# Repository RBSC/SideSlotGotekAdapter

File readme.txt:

--------------------------------------------
Gotek Adapter Module v1.1
Copyright (c) 2018 RBSC
Portions (c) Talent/Telematica
--------------------------------------------

WARNING! To avoid damage to the adapter and your MSX computer never insert or remove the adapter when a computer is powered on!

IMPORTANT! This adapter is compatible with MSX1, MSX2 and MSX2+ systems. However on MSX1 systems MSX-DOS may not start unless a
memory extension cartridge is inserted into one of the slots. 

IMPORTANT! The Gotek emulator must be secured by at least 2 screws (one from each side) in the adapter's case. Otherwise it will
be detached from the board if pulled by its case.

About
-----

This device is the adapter for the Gotek floppy emulator designed by RBSC based on their own Multicontroller as well as on the
TDC-600 controller that was originally designed by Talent/Telematica. The adapter was specifically made in the form of the side
slot cartidge, that can be used with Yamaha MSX YIS503, CX5M, CX5MII and similar MSX machines. The main idea was to introduce
the possibility to use real floppy disks or their images in the Gotek emulator on these diskless computers.

The adapter can be either used to host the Gotek emulator inside its body or to be used as the controller for the external floppy
disk drives. The Gotek emulator may be also used as the external device.

The adapter may be used with the 50-pin slot on any compatible MSX computer with the special 50-to-60 pin adapter cable or with
the original Yamaha's cartridge-based adapter. Please keep in mind that the Gotek emulator must have the FlashFloppy firmware.
The adapter was tested only with that firmware and the correct functionality is not guaranteed with any other firmware.

Usage with external devices
---------------------------

To be able to use the adapter with external devices, the special cover with holes for the floppy interface connector and for the
power connector must be used. The standard male-to-male 34-pin floppy connector with or without the cable locks should be used to
provide the interface for the external devices. It's recommended to use the connector with the "key" to avoid inserting the
interface cables upside down. As an option, a long floppy cable may be connected directly to the adapter's board (pads marked as
CN2) and stored inside the adapter's case (there's plenty of room there). However it's better to install the through-pin connector
and attach it to the board with wires. Also it may be a good idea to power the floppy drives from external source because certain
MSX computers may not be designed to power floppy drives from their internal power supplies. So if you power older floppy drives
from the adapter's power connector, your MSX's power supply may be loaded beyond its designed capacity. This is a low risk event,
but might still happen.

For the floppy's power connector it's best to use the 4-pin male-to-male audio connector with the lock (those were installed on
the older audio cards to connect them to the audio outputs of the older CD-ROM drives), but other connectors may be used as well.
It's better to use the connectors that can't be connected upside down and, as a result, supply 12v to the 5v circuit - this will
cause severe damage to the Gotek emulator or the floppy drive. This connector must be wired to the PWR pads on the board to provide
both 5v and 12v to the floppy drives. The floppy drives produced in the recent years as well as the Gotek emulator don't need 12v,
but older drives require it.

See the pictures in the PIC subfolder to check the connectors and the wiring of the external devices. Please note that the 720kb
drives must be configured as "A" and the straight floppy cable must be used for them. Those drives must be set as DS0, otherwise
they will not work. For the 1.44mb PC drives with DS1 or DS2 settings a twisted floppy cable must be used. Those PC drives could
be configured as either "A+B" or "B+A". See the "Jumper settings" chapter for more info.

Usage with internal devices
---------------------------

The adapter was originally designed to host the Gotek emulator inside its body. The emulator should be connected to the board
with the 34-pin dual row female connector with long pins. The power could be connected by either using the Molex connector with
its wires soldered to any PWR connector on board or with a single row 4-pin female connector with long pins. It's important to
remember that all internal connectors must have long pins so that they could reach the interface and power connectors of the Gotek
emulator that are located higher than the adapter's board. See the pictures in the PIC subfolder to check the connectors and the
wiring of the inserted Gotek emulator.

Normally the well-soldered power and floppy interface connectors will allow the emulator to be removed from the adapter's case
without too much effort. However inserting the emulator may bend the power connector or get the wrong connection to the floppy
interface pins, so it's highly recommended to open the adapter's case when inserting the emulator to make sure that both power
and interface connectors are properly aligned.

Jumper settings
---------------

The adapter has four 3-pin configuration jumper pins. All 4 of them must have one jumper installed at all times. On the board there
is a CFG table that shows jumper configurations for different drives.

When all 3-pin jumpers are set in the upper position, then a normal 1.44mb PC drive (with default DS1 setting) can be connected to
the board with the standard twisted interface cable. There can be maximum 2 drives connected to the adapter with the same cable. The
drive set as DS1 will be bootable (A:), the drive with DS2 setting will be used as the second drive (B:)

When all 3-pin jumpers are set in the lower position, then a normal 1.44mb PC drive (with default DS1 setting) can be connected to
the board with the standard twisted interface cable. There can be maximum 2 drives connected to the adapter with the same cable. The
drive set as DS2 will be bootable (A:), the drive with DS1 setting will be used as the second drive (B:)

When the 3-pin jumpers are set as shown for the "A" configuration, then a DS/DD 720kb drive set as DS0 or a Gotek emulator set as
DS0 can be connected to the adapter with the straight floppy cable (PC cable with a "twist" won't work). Only one drive may be
connected to the controller in this case. The operating system and certain programs will still allow to use 2 logical drives even if
one drive is connected, but a user will need to change the diskettes or switch the disk images manually when asked.

Selecting BIOS versions
-----------------------

There are 2 versions of disk BIOS available for the adapter - the original one (1.0) and the one translated into English (1.1).
There's a jumper on the board marked as "BIOS VER." that allows to select the desired BIOS version. When the jumper is installed,
the 1.0 version will be used, otherwise the 1.1 version will be used. The version number will be shown when a computer boots into
MSX Basic. Please note that  these BIOSes are capable of working with the 5.25 inch floppy drives, but RBSC was not testing the
adapter with those drives. So if you are using the 5.25 inch drive with the adapter, you are doing this on your own risk.

Notes
-----

The adapter may not load certain games, disk images or boot to certain operating system versions because of the limitations of the
original TDC-600 controller and its firmware. The design of the TDC controller was simplified to have less electronic components,
so its functionality differs from the standard floppy controllers. Certain incompatibility issues will be observed.

The 3D models of the adapter's case, bottom and side cover are provided in the STL format for self-printing. They can be printed on
any 3D printer with PLA or ABS. The recommended settings are 0.2mm layer thickness, supports on, 25% infill, 25% supports, heated
bed and a hood over the printer (to avoid deformations). The case and the bottom cover parts must be printed with their open sides
facing upwards to avoid too many supports and the damage of the screw holders when removing those supports.

The bottom cover should be attached to the body with 3.0mm x 10mm screws with flat heads. It's recommended not to tighten the screws
too much to avoid breaking the threads inside the screw holders. Also keep in mind that the cover is made out of plastic (unlike
the original SFG case's cover), so it needs a bit more gentle handling.

The Gotek emulator needs to be secured inside the adapter's case by two or (better) four 3.0mm x 15mm screws with flat or conical
heads. It's recommended not to tighten the screws too much to avoid breaking the threads inside the Gotek's case.

If you are assembling the adapter with external connectors yourself, please note that it's better to solder the wires between the
board and the connectors. If you use Dupont connectors (like on the images) and jumper pins, you will need to remove the plactic
parts of the pins and cut the 2mm tops of all the pins. Otherwise you won't be able to connect the Dupont connectors to the board. 

IMPORTANT!
----------

The RBSC provides all the files and information for free, without any liability (see the disclaimer.txt file). The provided information,
software or hardware must not be used for commercial purposes unless permitted by the RBSC. Producing a small amount of bare boards for
personal projects and selling the rest of the batch is allowed without the permission of RBSC.

When the sources of the tools are used to create alternative projects, please always mention the original source and the copyright!

Contact information
-------------------

The members of RBSC group Wierzbowsky, Tnt23, Ptero, Pencioner and DJS3000 can be contacted via the MSX.ORG or ZX-PK.RU forums. Just
send a personal message and state your business.

The RBSC repository can be found here:

https://github.com/rbsc

The MSX-related 3D models published by RBSC can be found here:

https://www.thingiverse.com/groups/rbsc/things

-= ! MSX FOREVER ! =-

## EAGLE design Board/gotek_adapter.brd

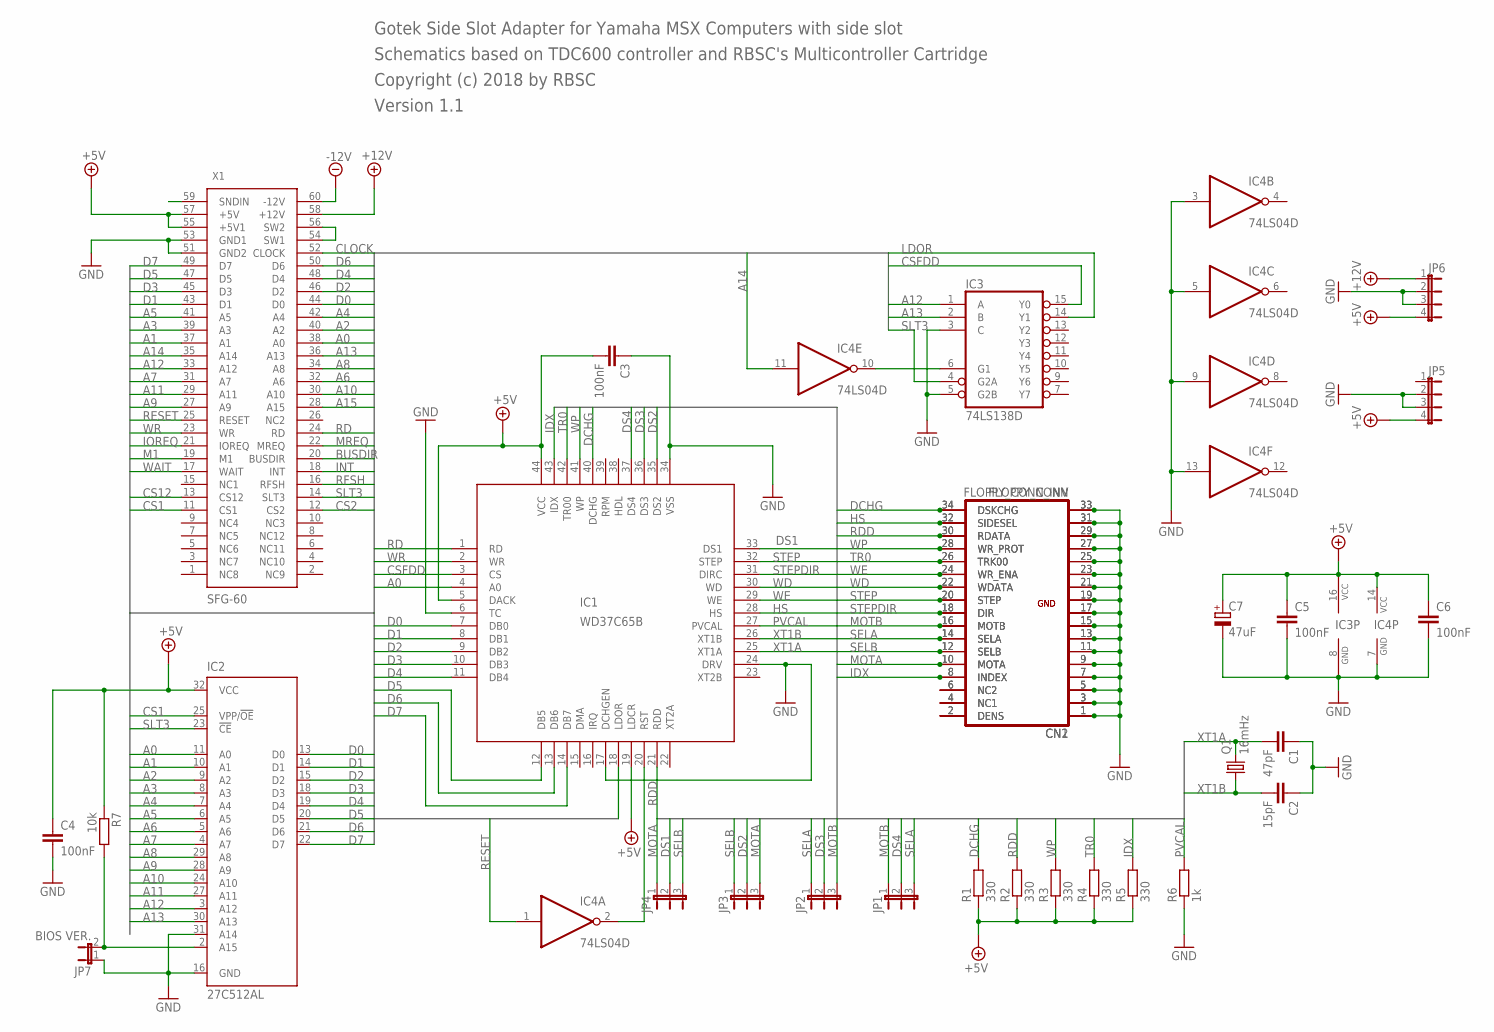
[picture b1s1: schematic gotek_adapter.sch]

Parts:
C1: 47pF; C0805
C2: 15pF; C0805
C3, C4, C5, C6: 100nF; C0805
C7: 47uF; SMC_D
CN1: FLOPPY_CONN; FL_CONN
CN2: FLOPPY_CONN_INV; FL_CONN
IC1: WD37C65B; PLCC44
IC2: 27C512AL; PLCC-32
IC3: 74LS138D; SO16
IC4: 74LS04D; SO14
JP1, JP2, JP3, JP4: JP2E; JP2
JP5, JP6: JP4E; JP4
JP7: BIOS VER.; JP1
Q1: 16mHz; HC49/S
R1, R2, R3, R4, R5: 330; R0805
R6: 1k; R0805
R7: 10k; R0805
X1: SFG-60

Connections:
+5V: C3.2, C4.1, C5.1, C6.1, C7.+, IC1.5 (DACK), IC1.19 (LDCR), IC1.44 (VCC), IC2.32 (VCC), IC3.16 (VCC), IC4.14 (VCC), JP5.4, JP6.4, R1.1, R2.1, R3.1, R4.1, R5.1, R7.1, X1.55 (+5V1), X1.57 (+5V)
+12V: JP6.1, X1.58 (+12V)
-12V: X1.60 (-12V)
A0: IC1.4 (A0), IC2.11 (A0), X1.38 (A0)
A1: IC2.10 (A1), X1.37 (A1)
A2: IC2.9 (A2), X1.40 (A2)
A3: IC2.8 (A3), X1.39 (A3)
A4: IC2.7 (A4), X1.42 (A4)
A5: IC2.6 (A5), X1.41 (A5)
A6: IC2.5 (A6), X1.32 (A6)
A7: IC2.4 (A7), X1.31 (A7)
A8: IC2.29 (A8), X1.34 (A8)
A9: IC2.28 (A9), X1.27 (A9)
A10: IC2.24 (A10), X1.30 (A10)
A11: IC2.27 (A11), X1.29 (A11)
A12: IC2.3 (A12), IC3.1 (A), X1.33 (A12)
A13: IC2.30 (A13), IC3.2 (B), X1.36 (A13)
A14: IC4.11 (I), X1.35 (A14)
A15: X1.28 (A15)
BUSDIR: X1.20 (BUSDIR)
CLOCK: X1.52 (CLOCK)
CS1: IC2.25 (VPP/!OE), X1.11 (CS1)
CS2: X1.12 (CS2)
CS12: X1.13 (CS12)
CSFDD: IC1.3 (CS), IC3.15 (Y0)
D0: IC1.7 (DB0), IC2.13 (D0), X1.44 (D0)
D1: IC1.8 (DB1), IC2.14 (D1), X1.43 (D1)
D2: IC1.9 (DB2), IC2.15 (D2), X1.46 (D2)
D3: IC1.10 (DB3), IC2.18 (D3), X1.45 (D3)
D4: IC1.11 (DB4), IC2.19 (D4), X1.48 (D4)
D5: IC1.12 (DB5), IC2.20 (D5), X1.47 (D5)
D6: IC1.13 (DB6), IC2.21 (D6), X1.50 (D6)
D7: IC1.14 (DB7), IC2.22 (D7), X1.49 (D7)
DCHG: CN1.34 (DSKCHG), CN2.34 (DSKCHG), IC1.40 (DCHG), R1.2
DS1: IC1.33 (DS1), JP4.2
DS2: IC1.35 (DS2), JP3.2
DS3: IC1.36 (DS3), JP2.2
DS4: IC1.37 (DS4), JP1.2
GND: C1.1, C2.1, C3.1, C4.2, C5.2, C6.2, C7.-, CN1.1, CN1.3, CN1.5, CN1.7, CN1.9, CN1.11, CN1.13, CN1.15, CN1.17, CN1.19, CN1.21, CN1.23, CN1.25, CN1.27, CN1.29, CN1.31, CN1.33, CN2.1, CN2.3, CN2.5, CN2.7, CN2.9, CN2.11, CN2.13, CN2.15, CN2.17, CN2.19, CN2.21, CN2.23, CN2.25, CN2.27, CN2.29, CN2.31, CN2.33, IC1.6 (TC), IC1.17 (DCHGEN), IC1.24 (DRV), IC1.34 (VSS), IC2.16 (GND), IC2.31 (A14), IC3.3 (C), IC3.5 (G2B), IC3.8 (GND), IC4.3 (I), IC4.5 (I), IC4.7 (GND), IC4.9 (I), IC4.13 (I), JP5.2, JP5.3, JP6.2, JP6.3, JP7.1, R6.1, X1.51 (GND2), X1.53 (GND1)
HS: CN1.32 (SIDESEL), CN2.32 (SIDESEL), IC1.28 (HS)
IDX: CN1.8 (INDEX), CN2.8 (INDEX), IC1.43 (IDX), R5.2
INT: X1.18 (INT)
IOREQ: X1.21 (IOREQ)
LDOR: IC1.18 (LDOR), IC3.14 (Y1)
M1: X1.19 (M1)
MOTA: CN1.10 (MOTA), CN2.10 (MOTA), JP3.3, JP4.1
MOTB: CN1.16 (MOTB), CN2.16 (MOTB), JP1.1, JP2.3
MREQ: X1.22 (MREQ)
unnamed: IC1.20 (RST), IC4.2 (O)
unnamed: IC3.6 (G1), IC4.10 (O)
unnamed: X1.54 (SW1), X1.56 (SW2)
unnamed: CN1.2 (DENS), CN2.2 (DENS)
unnamed: IC2.2 (A15), JP7.2, R7.2
unnamed: CN1.4 (NC1), CN2.4 (NC1)
unnamed: CN1.6 (NC2), CN2.6 (NC2)
PVCAL: IC1.27 (PVCAL), R6.2
RD: IC1.1 (RD), X1.24 (RD)
RDD: CN1.30 (RDATA), CN2.30 (RDATA), IC1.21 (RDD), R2.2
RESET: IC4.1 (I), X1.25 (RESET)
RFSH: X1.16 (RFSH)
SELA: CN1.14 (SELA), CN2.14 (SELA), JP1.3, JP2.1
SELB: CN1.12 (SELB), CN2.12 (SELB), JP3.1, JP4.3
SLT3: IC2.23 (!CE), IC3.4 (G2A), X1.14 (SLT3)
STEP: CN1.20 (STEP), CN2.20 (STEP), IC1.32 (STEP)
STEPDIR: CN1.18 (DIR), CN2.18 (DIR), IC1.31 (DIRC)
TR0: CN1.26 (TRK00), CN2.26 (TRK00), IC1.42 (TR00), R4.2
WAIT: X1.17 (WAIT)
WD: CN1.22 (WDATA), CN2.22 (WDATA), IC1.30 (WD)
WE: CN1.24 (WR_ENA), CN2.24 (WR_ENA), IC1.29 (WE)
WP: CN1.28 (WR_PROT), CN2.28 (WR_PROT), IC1.41 (WP), R3.2
WR: IC1.2 (WR), X1.23 (WR)
XT1A: C1.2, IC1.25 (XT1A), Q1.2
XT1B: C2.2, IC1.26 (XT1B), Q1.1

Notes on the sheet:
Gotek Side Slot Adapter for Yamaha MSX Computers with side slot
Schematics based on TDC600 controller and RBSC's Multicontroller Cartridge
Copyright (c) 2018 by RBSC
Version 1.1

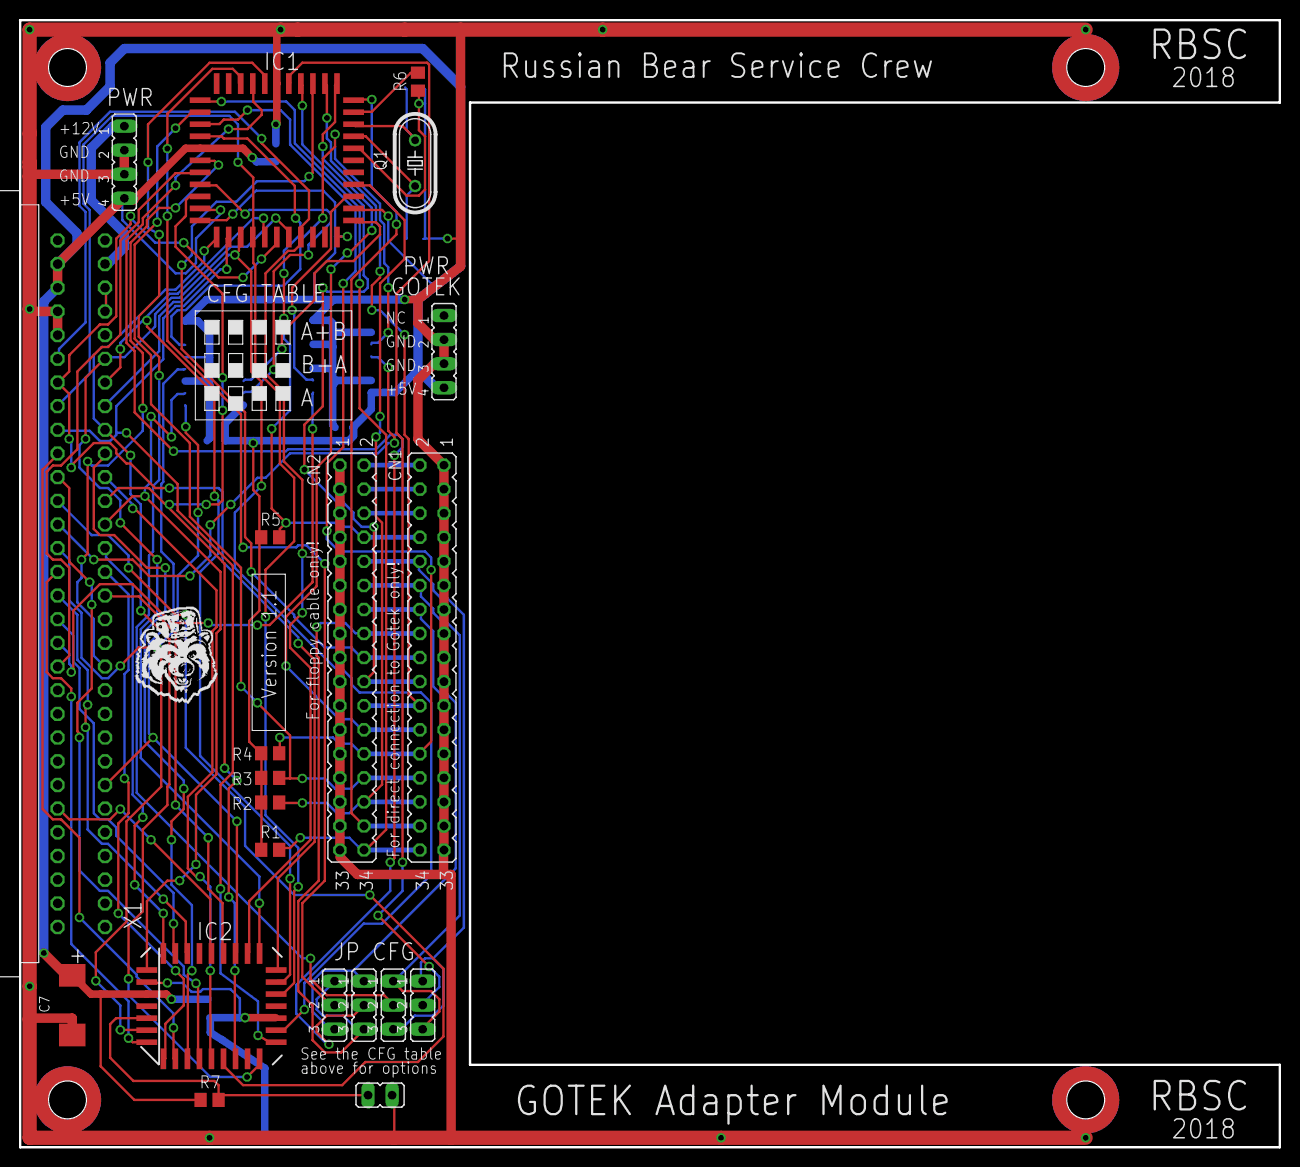
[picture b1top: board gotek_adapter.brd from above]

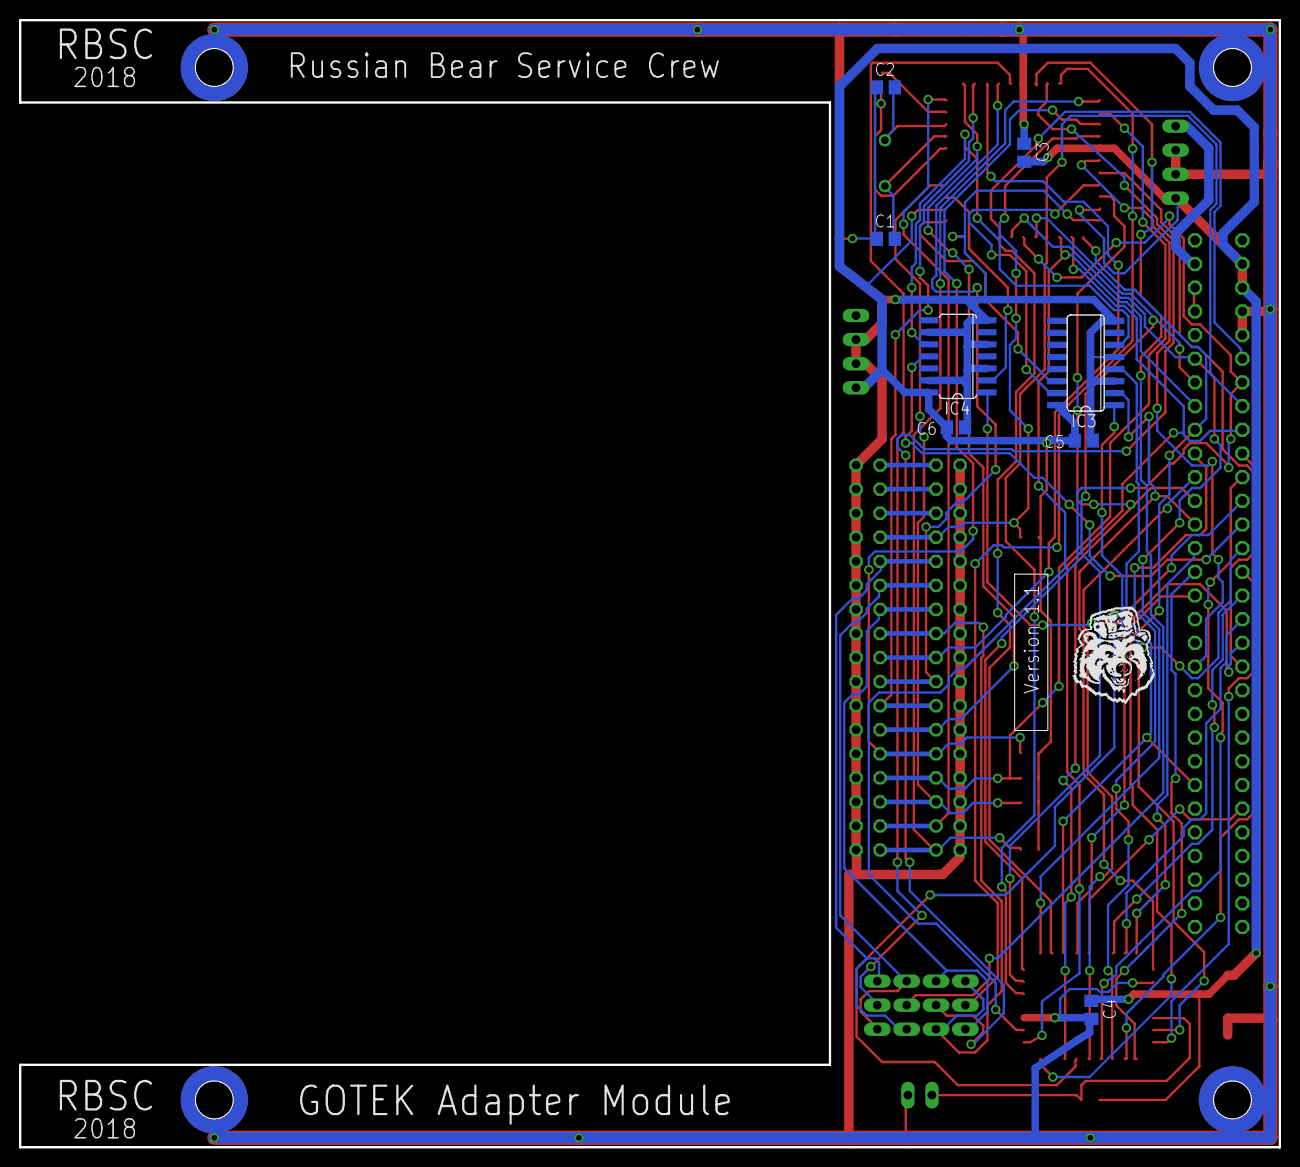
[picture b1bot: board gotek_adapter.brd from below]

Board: 2 copper layers, 133.0 x 119.0 mm, 29 parts (8 on the bottom side), 61 nets.

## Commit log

2019-01-26 :space_invader: Added .gitattributes & .gitignore files
2019-01-27 Release 28.01.2019
    Initial release. Board, schematics, Gerbers, case, BIOS, pictures.
2019-03-28 Updated 28.03.2019
    Reduced screw holes by 1mm.
2019-04-12 Update 12.04.2019
    Added an archive with Gotek configuration file and a pair of DSK images
    with tools and PSG music
2019-04-21 Update 21.04.2019
    Added models of Gotek holders that fix the emulator inside the case and
    the pictures of the installation.
2019-05-01 Updated 01.05.2019
    Added a bit corrected model and the source file for the model that can
    be edited in Fusion 360
2019-08-09 Updated 09.08.2019
    Corrected readme instructions concerning fixing the Gotek inside the
    case
2020-06-30 Updated 30.06.2020
    Size correction
